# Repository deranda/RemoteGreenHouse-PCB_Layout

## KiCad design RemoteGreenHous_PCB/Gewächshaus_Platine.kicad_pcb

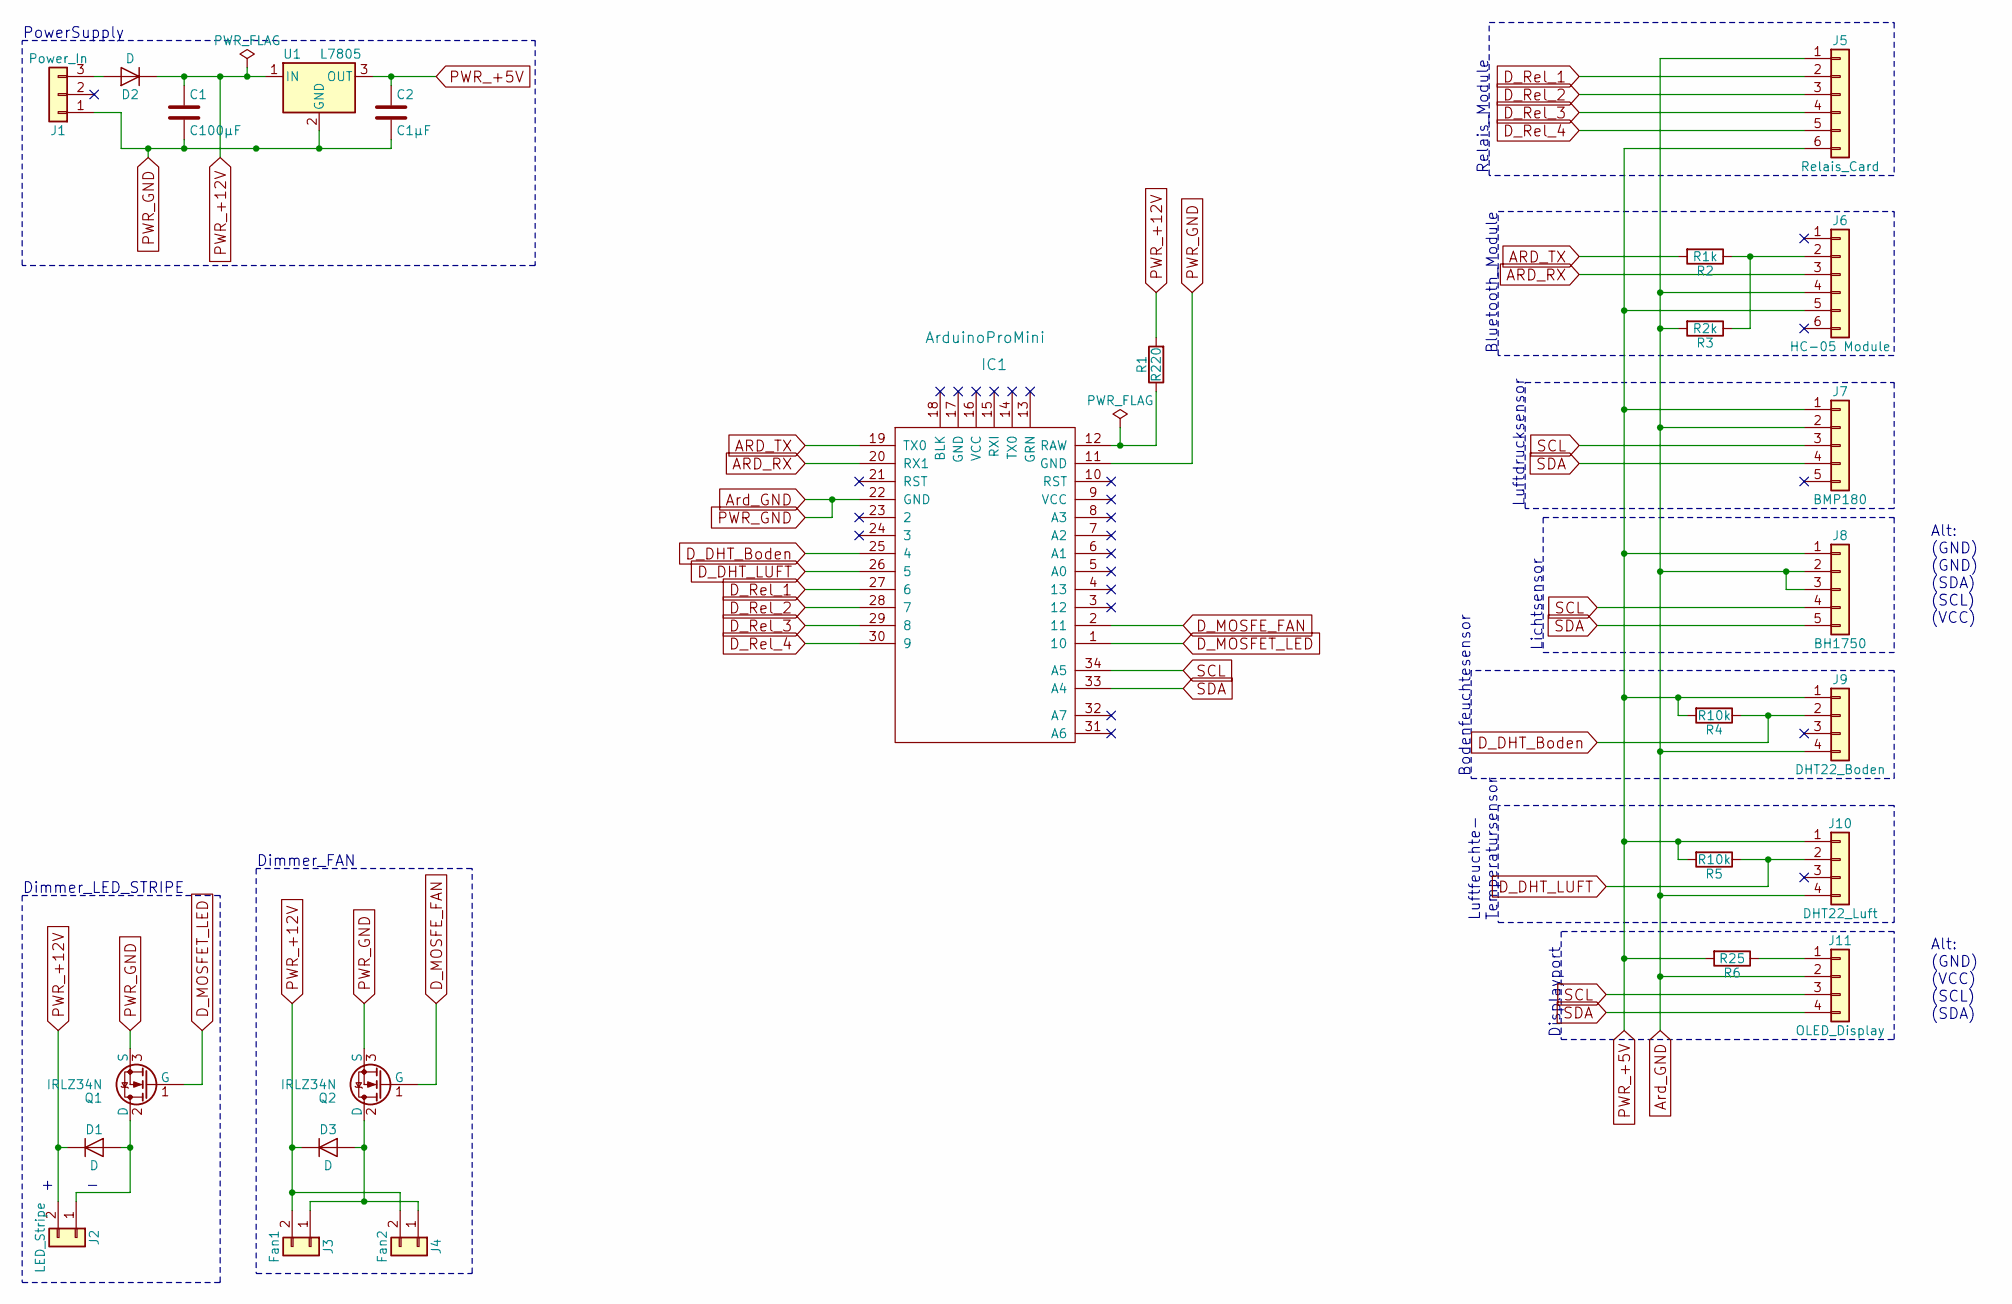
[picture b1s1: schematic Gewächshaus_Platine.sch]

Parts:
C1: C100µF; C_Disc_D3.0mm_W1.6mm_P2.50mm
C2: C1µF; C_Disc_D3.0mm_W1.6mm_P2.50mm
D1, D2, D3: D; D_DO-41_SOD81_P7.62mm_Horizontal
IC1: ArduinoProMini
J1: Power_In; Pin_Header_Straight_1x03_Pitch2.54mm
J2: LED_Stripe; Pin_Header_Straight_1x02_Pitch2.54mm
J3: Fan1; Pin_Header_Straight_1x02_Pitch2.54mm
J4: Fan2; Pin_Header_Straight_1x02_Pitch2.54mm
J5: Relais_Card; Pin_Header_Straight_1x06_Pitch2.54mm
J6: HC-05 Module; Pin_Header_Straight_1x06_Pitch2.54mm
J7: BMP180; Pin_Header_Straight_1x05_Pitch2.54mm
J8: BH1750; Pin_Header_Straight_1x05_Pitch2.54mm
J9: DHT22_Boden; Pin_Header_Straight_1x04_Pitch2.54mm
J10: DHT22_Luft; Pin_Header_Straight_1x04_Pitch2.54mm
J11: OLED_Display; Pin_Header_Straight_1x04_Pitch2.54mm
Q1, Q2: IRLZ34N; TO-220-3_Vertical
R1: R220; R_Axial_DIN0207_L6.3mm_D2.5mm_P7.62mm_Horizontal
R2: R1k; R_Axial_DIN0207_L6.3mm_D2.5mm_P7.62mm_Horizontal
R3: R2k; R_Axial_DIN0207_L6.3mm_D2.5mm_P7.62mm_Horizontal
R4, R5: R10k; R_Axial_DIN0207_L6.3mm_D2.5mm_P7.62mm_Horizontal
R6: R25; R_Axial_DIN0207_L6.3mm_D2.5mm_P7.62mm_Horizontal
U1: L7805; TO-220-3_Vertical

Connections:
ARD_RX: IC1.20 (RX1), J6.3
ARD_TX: IC1.19 (TX0), R2.2
Ard_GND: C1.2, C2.2, IC1.11 (GND), IC1.22 (GND), J1.1, J5.1, J6.4, J7.2, J8.2, J8.3, J9.4, J10.4, J11.2, Q1.3 (S), Q2.3 (S), R3.2, U1.2 (GND); also elsewhere on the board
D_DHT_Boden: IC1.25 (4), J9.2, R4.1
D_DHT_LUFT: IC1.26 (5), J10.2, R5.1
D_MOSFET_LED: IC1.1 (10), Q1.1 (G)
D_MOSFE_FAN: IC1.2 (11), Q2.1 (G)
D_Rel_1: IC1.27 (6), J5.2
D_Rel_2: IC1.28 (7), J5.3
D_Rel_3: IC1.29 (8), J5.4
D_Rel_4: IC1.30 (9), J5.5
unnamed: D1.2 (A), J2.1, Q1.2 (D)
unnamed: D2.2 (A), J1.3
unnamed: D3.2 (A), J3.1, J4.1, Q2.2 (D)
unnamed: IC1.12 (RAW), R1.1
unnamed: J6.2, R2.1, R3.1
unnamed: J11.1, R6.1
PWR_+5V: C2.1, J5.6, J6.5, J7.1, J8.1, J9.1, J10.1, R4.2, R5.2, R6.2, U1.3 (OUT); also elsewhere on the board
PWR_+12V: C1.1, D1.1 (K), D2.1 (K), D3.1 (K), J2.2, J3.2, J4.2, R1.2, U1.1 (IN); also elsewhere on the board
SCL: IC1.34 (A5), J7.3, J8.4, J11.3
SDA: IC1.33 (A4), J7.4, J8.5, J11.4

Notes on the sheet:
PowerSupply
Dimmer_LED_STRIPE
Dimmer_FAN
Relais_Module
Bluetooth_Module
Luftdrucksensor
Lichtsensor
Bodenfeuchtesensor
Luftfeuchte- Temperatursensor
Displayport
Alt: (GND) (GND) (SDA) (SCL) (VCC)
Alt: (GND) (VCC) (SCL) (SDA)

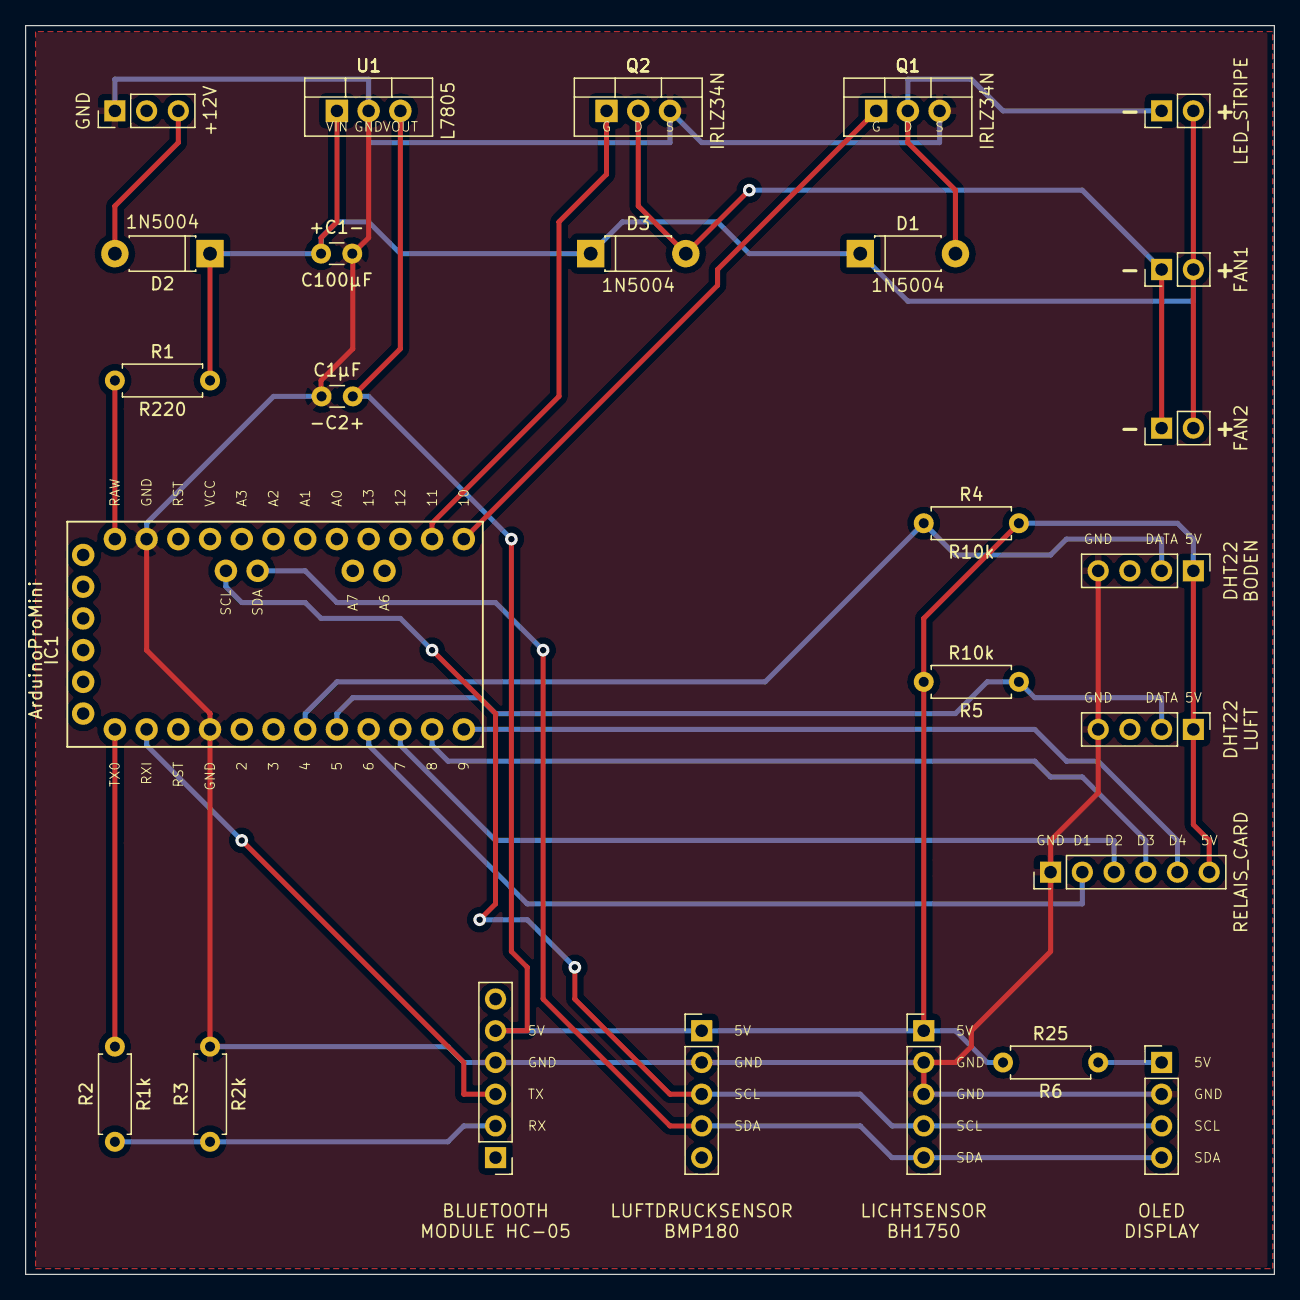
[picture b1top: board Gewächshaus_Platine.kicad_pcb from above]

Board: 2 copper layers, 100.0 x 100.0 mm, 26 parts (0 on the bottom side), 21 nets.

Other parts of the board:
+C1-: C100µF; C_Disc_D3.0mm_W1.6mm_P2.50mm
-C2+: C1µF; C_Disc_D3.0mm_W1.6mm_P2.50mm

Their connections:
Ard_GND: +C1-.2, -C2+.2; also elsewhere on the board
PWR_+5V: -C2+.1; also elsewhere on the board
PWR_+12V: +C1-.1; also elsewhere on the board

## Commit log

2018-03-09 Initial Upload
